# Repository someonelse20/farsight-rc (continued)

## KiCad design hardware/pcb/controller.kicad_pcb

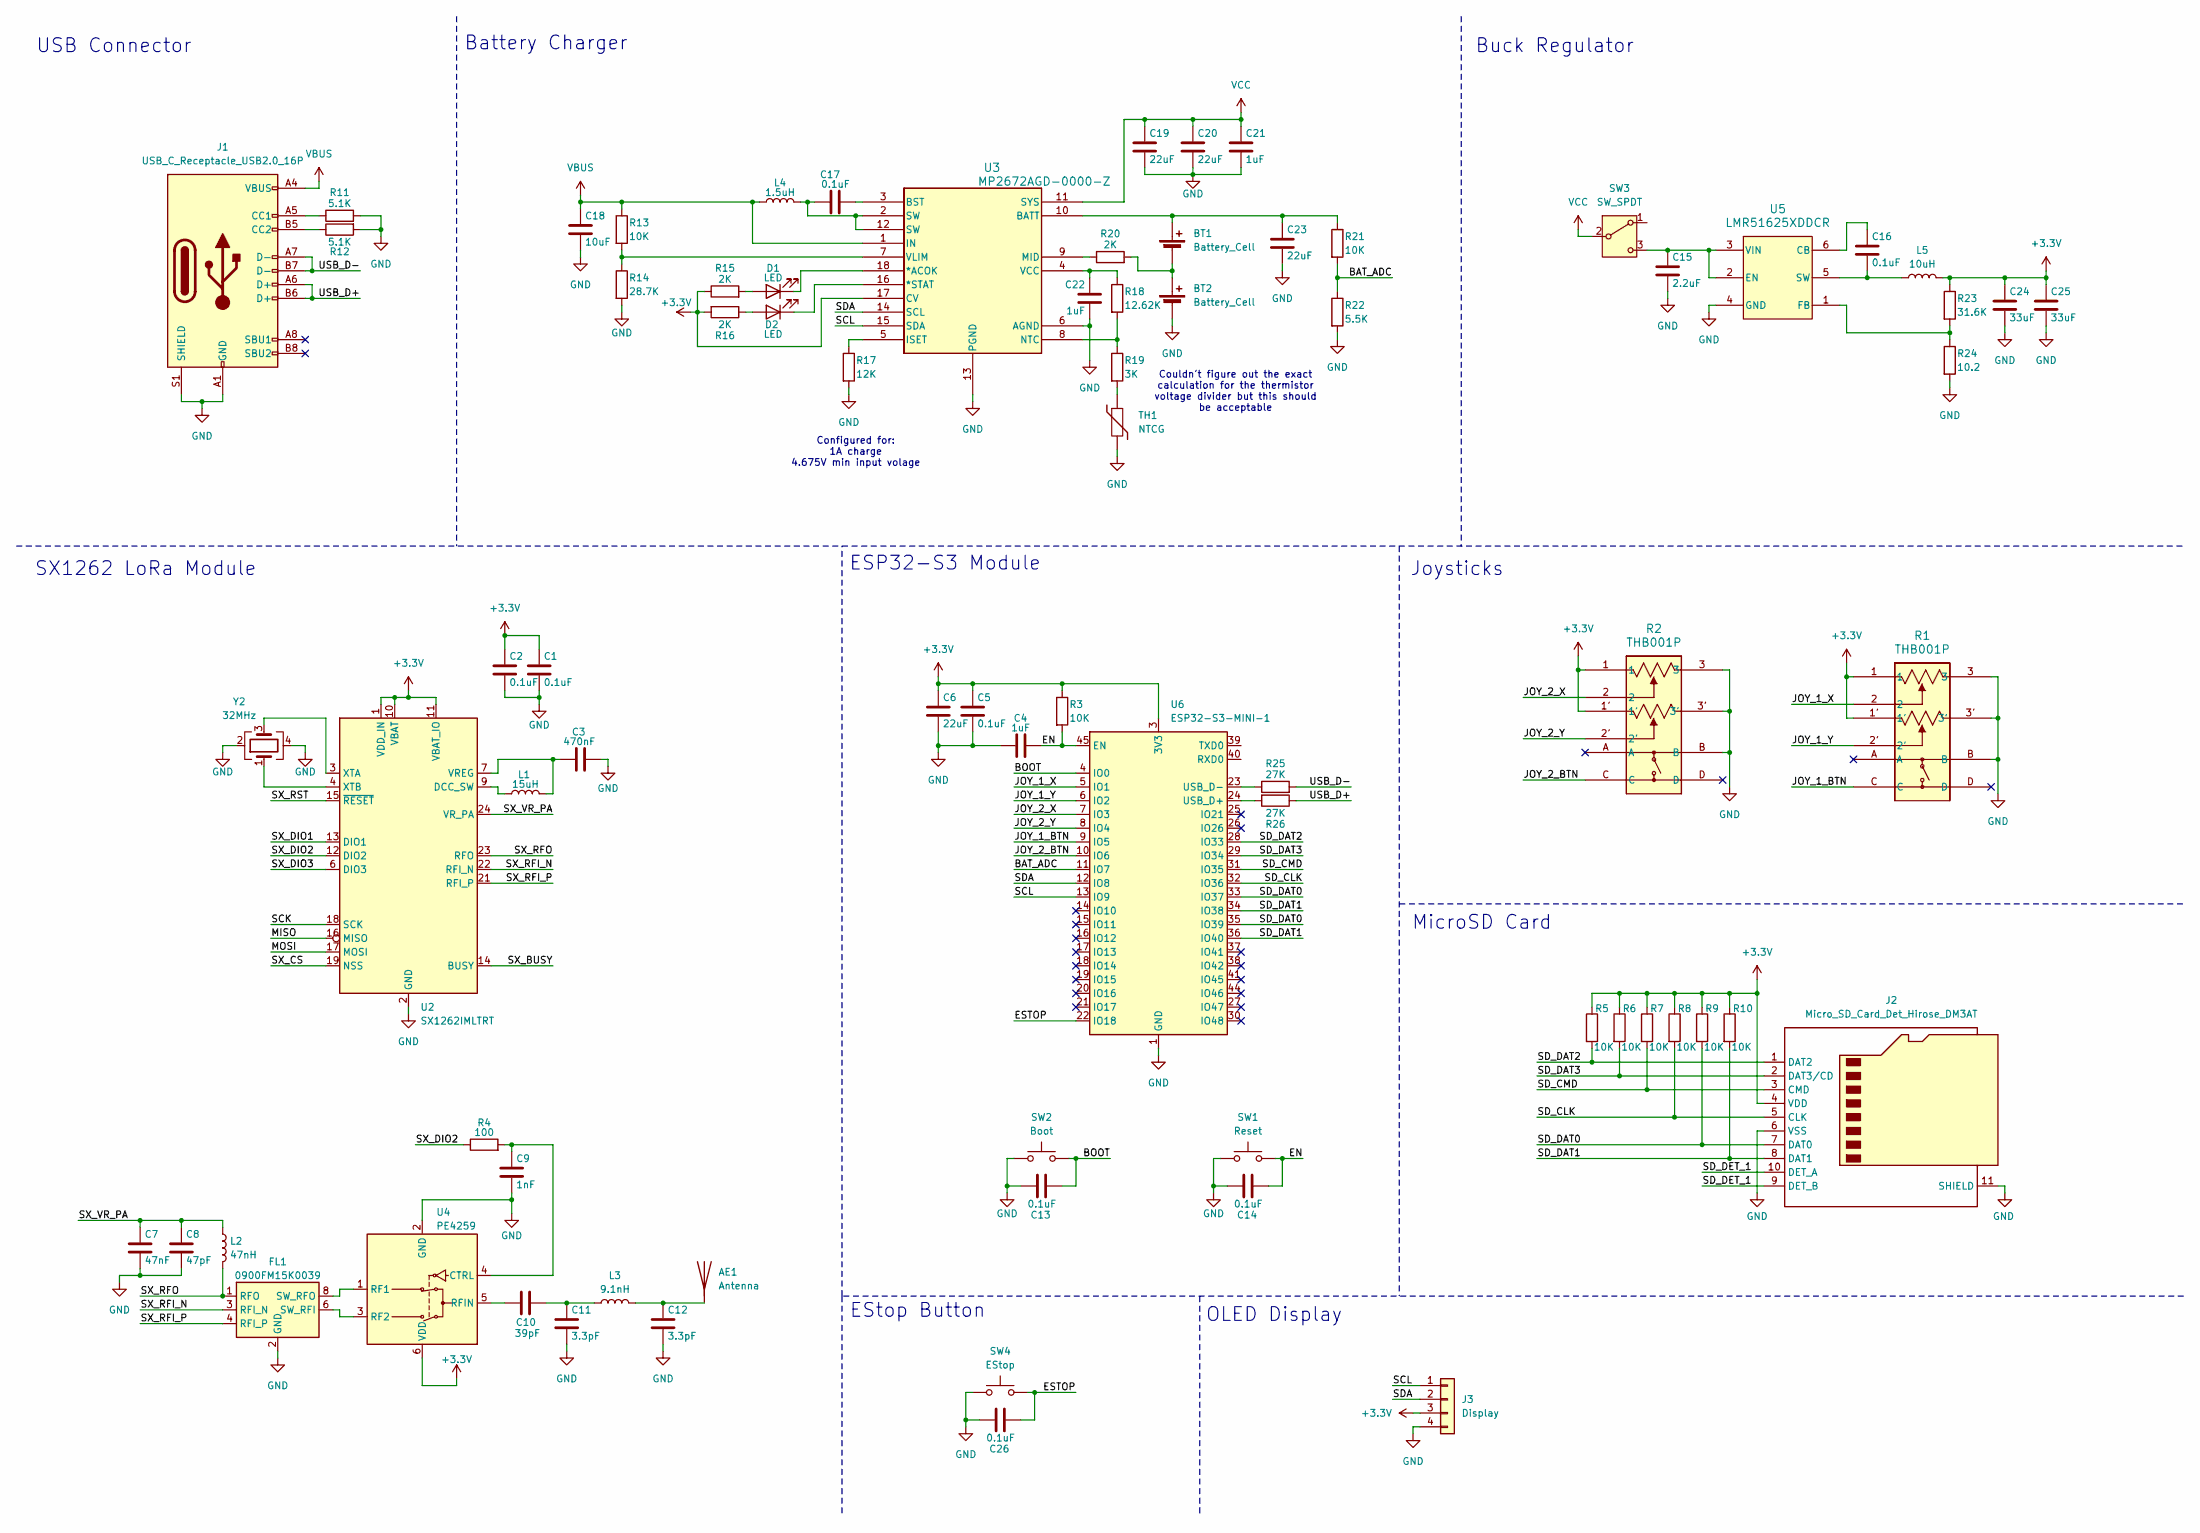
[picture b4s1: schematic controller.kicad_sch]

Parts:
AE1: Antenna; SMA_Amphenol_901-143_Horizontal
BT1, BT2: Battery_Cell; BatteryHolder_MPD_BH-18650-PC
C1, C2, C5, C13, C14, C16, C17, C26: 0.1uF; C_0402_1005Metric
C3: 470nF; C_0402_1005Metric
C4, C21, C22: 1uF; C_0402_1005Metric
C6, C19, C20: 22uF; C_0603_1608Metric
C7: 47nF; C_0402_1005Metric
C8: 47pF; C_0402_1005Metric
C9: 1nF; C_0402_1005Metric
C10: 39pF; C_0402_1005Metric
C11, C12: 3.3pF; C_0402_1005Metric
C15: 2.2uF; C_0402_1005Metric
C18: 10uF; C_0603_1608Metric
C23: 22uF; C_0805_2012Metric
C24, C25: 33uF; C_0603_1608Metric
D1, D2: LED; LED_D3.0mm
FL1: 0900FM15K0039; Balun_Johanson_0900FM15K0039
J1: USB_C_Receptacle_USB2.0_16P; USB_C_Receptacle_GCT_USB4105-xx-A_16P_TopMnt_Horizontal
J2: Micro_SD_Card_Det_Hirose_DM3AT; microSD_HC_Hirose_DM3AT-SF-PEJM5
J3: Display; JST_PH_S4B-PH-K_1x04_P2.00mm_Horizontal
L1: 15uH; L_0402_1005Metric
L2: 47nH; L_0402_1005Metric
L3: 9.1nH; L_0402_1005Metric
L4: 1.5uH; L_6.3x6.3_H3
L5: 10uH; L_APV_ANR4010
R1, R2: THB001P; THB001P_CNK
R3, R5, R6, R7, R8, R9, R10, R13, R21: 10K; R_0402_1005Metric
R4: 100; R_0402_1005Metric
R11, R12: 5.1K; R_0402_1005Metric
R14: 28.7K; R_0402_1005Metric
R15, R16, R20: 2K; R_0402_1005Metric
R17: 12K; R_0402_1005Metric
R18: 12.62K; R_0402_1005Metric
R19: 3K; R_0402_1005Metric
R22: 5.5K; R_0402_1005Metric
R23: 31.6K; R_0402_1005Metric
R24: 10.2; R_0402_1005Metric
R25, R26: 27K; R_0402_1005Metric
SW1: Reset; SW_Push_SPST_NO_Alps_SKRK
SW2: Boot; SW_Push_SPST_NO_Alps_SKRK
SW3: SW_SPDT; SW_Slide_SPDT_Straight_CK_OS102011MS2Q
SW4: EStop; SW_Push_SPST_NO_Alps_SKRK
TH1: NTCG; R_0402_1005Metric
U2: SX1262IMLTRT; QFN-24-1EP_4x4mm_P0.5mm_EP2.6x2.6mm
U3: MP2672AGD-0000-Z; QFN-18_MP2672A_MNP
U4: PE4259; SOT-363_SC-70-6
U5: LMR51625XDDCR; SOT-23-6
U6: ESP32-S3-MINI-1; ESP32-S2-MINI-1
Y2: 32MHz; Crystal_SMD_3225-4Pin_3.2x2.5mm

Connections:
+3.3V: C1.1, C2.1, C5.1, C6.1, C24.1, C25.1, J2.4 (VDD), J3.3, L5.2, R1.1, R1.1', R2.1, R2.1', R3.1, R5.1, R6.1, R7.1, R8.1, R9.1, R10.1, R15.1, R16.2, R23.1, U2.1 (VDD_IN), U2.10 (VBAT), U2.11 (VBAT_IO), U3.17 (CV), U4.6 (VDD), U6.3 (3V3)
/BAT_ADC: R21.2, R22.1, U6.11 (IO7)
/BOOT: C13.2, SW2.2, U6.4 (IO0)
/EN: C4.2, C14.2, R3.2, SW1.2, U6.45 (EN)
/ESTOP: C26.2, SW4.2, U6.22 (IO18)
/JOY_1_BTN: R1.C, U6.9 (IO5)
/JOY_1_X: R1.2, U6.5 (IO1)
/JOY_1_Y: R1.2', U6.6 (IO2)
/JOY_2_BTN: R2.C, U6.10 (IO6)
/JOY_2_X: R2.2, U6.7 (IO3)
/JOY_2_Y: R2.2', U6.8 (IO4)
/MISO: U2.16 (MISO)
/MOSI: U2.17 (MOSI)
/SCK: U2.18 (SCK)
/SCL: J3.1, U3.15 (SDA), U6.13 (IO9)
/SDA: J3.2, U3.14 (SCL), U6.12 (IO8)
/SD_CLK: J2.5 (CLK), R8.2, U6.32 (IO36)
/SD_CMD: J2.3 (CMD), R7.2, U6.31 (IO35)
/SD_DAT0: J2.7 (DAT0), R9.2, U6.33 (IO37), U6.35 (IO39)
/SD_DAT1: J2.8 (DAT1), R10.2, U6.34 (IO38), U6.36 (IO40)
/SD_DAT2: J2.1 (DAT2), R5.2, U6.28 (IO33)
/SD_DAT3: J2.2 (DAT3/CD), R6.2, U6.29 (IO34)
/SD_DET_1: J2.9 (DET_B), J2.10 (DET_A)
/SX_BUSY: U2.14 (BUSY)
/SX_CS: U2.19 (NSS)
/SX_DIO1: U2.13 (DIO1)
/SX_DIO2: R4.1, U2.12 (DIO2)
/SX_DIO3: U2.6 (DIO3)
/SX_RFI_N: FL1.3 (RFI_N), U2.22 (RFI_N)
/SX_RFI_P: FL1.4 (RFI_P), U2.21 (RFI_P)
/SX_RFO: FL1.1 (RFO), L2.2, U2.23 (RFO)
/SX_RST: U2.15 (~RESET)
/SX_VR_PA: C7.1, C8.1, L2.1, U2.24 (VR_PA)
/USB_D+: J1.A6 (D+), J1.B6 (D+), R26.1
/USB_D-: J1.A7 (D-), J1.B7 (D-), R25.2
GND: BT2.2 (-), C1.2, C2.2, C3.2, C4.1, C5.2, C6.2, C7.2, C8.2, C9.2, C11.2, C12.2, C13.1, C14.1, C15.2, C18.2, C19.2, C20.2, C21.2, C22.2, C23.2, C24.2, C25.2, C26.1, FL1.2 (GND), FL1.5 (GND), FL1.7 (GND), FL1.9 (GND), FL1.10 (GND), J1.A1 (GND), J1.A12 (GND), J1.B1 (GND), J1.B12 (GND), J1.S1 (SHIELD), J2.6 (VSS), J2.11 (SHIELD), J3.4, R1.3, R1.3', R1.B, R2.3, R2.3', R2.B, R11.2, R12.2, R14.2, R17.2, R22.2, R24.2, SW1.1, SW2.1, SW4.1, TH1.2, U2.2 (GND), U2.5 (GND), U2.8 (GND), U2.20 (GND), U2.25 (GND), U3.6 (AGND), U3.13 (PGND), U4.2 (GND), U5.4 (GND), U6.1 (GND), U6.2 (GND), U6.42 (GND), U6.43 (GND), U6.46 (GND), U6.47 (GND), U6.48 (GND), U6.49 (GND), U6.50 (GND), U6.51 (GND), U6.52 (GND), U6.53 (GND), U6.54 (GND), U6.55 (GND), U6.56 (GND), U6.57 (GND), U6.58 (GND), U6.59 (GND), U6.60 (GND), U6.61 (GND), U6.62 (GND), U6.63 (GND), U6.64 (GND), U6.65 (GND), Y2.2, Y2.4
unnamed: AE1.1 (A), C12.1, L3.2
unnamed: BT1.1 (+), C23.1, R21.1, U3.10 (BATT)
unnamed: BT1.2 (-), BT2.1 (+), R20.2
unnamed: C10.2, C11.1, L3.1
unnamed: C17.1, L4.2, U3.2 (SW), U3.12 (SW)
unnamed: D1.2 (A), R15.2
unnamed: D1.1 (K), U3.18 (*ACOK)
unnamed: D2.2 (A), R16.1
unnamed: D2.1 (K), U3.16 (*STAT)
unnamed: FL1.6 (SW_RFI), U4.3 (RF2)
unnamed: FL1.8 (SW_RFO), U4.1 (RF1)
unnamed: J1.A5 (CC1), R11.1
unnamed: J1.B5 (CC2), R12.1
unnamed: R19.2, TH1.1
unnamed: C15.1, SW3.3 (C), U5.2 (EN), U5.3 (VIN)
unnamed: L1.1, U2.9 (DCC_SW)
unnamed: C3.1, L1.2, U2.7 (VREG)
unnamed: U2.3 (XTA), Y2.3
unnamed: U2.4 (XTB), Y2.1
unnamed: C17.2, U3.3 (BST)
unnamed: R17.1, U3.5 (ISET)
unnamed: R20.1, U3.9 (MID)
unnamed: R18.2, R19.1, U3.8 (NTC)
unnamed: C22.1, R18.1, U3.4 (VCC)
unnamed: R13.2, R14.1, U3.7 (VLIM)
unnamed: C9.1, R4.2, U4.4 (CTRL)
unnamed: C10.1, U4.5 (RFIN)
unnamed: C16.1, U5.6 (CB)
unnamed: R23.2, R24.1, U5.1 (FB)
unnamed: C16.2, L5.1, U5.5 (SW)
unnamed: R26.2, U6.24 (USB_D+)
unnamed: R25.1, U6.23 (USB_D-)
VBUS: C18.1, J1.A4 (VBUS), J1.A9 (VBUS), J1.B4 (VBUS), J1.B9 (VBUS), L4.1, R13.1, U3.1 (IN)
VCC: C19.1, C20.1, C21.1, SW3.2 (B), U3.11 (SYS)

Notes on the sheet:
Buck Regulator
ESP32-S3 Module
Joysticks
EStop Button
Couldn't figure out the exact calculation for the thermistor voltage divider but this should be acceptable
USB Connector
Battery Charger
SX1262 LoRa Module
OLED Display
Configured for: 1A charge 4.675V min input volage
MicroSD Card

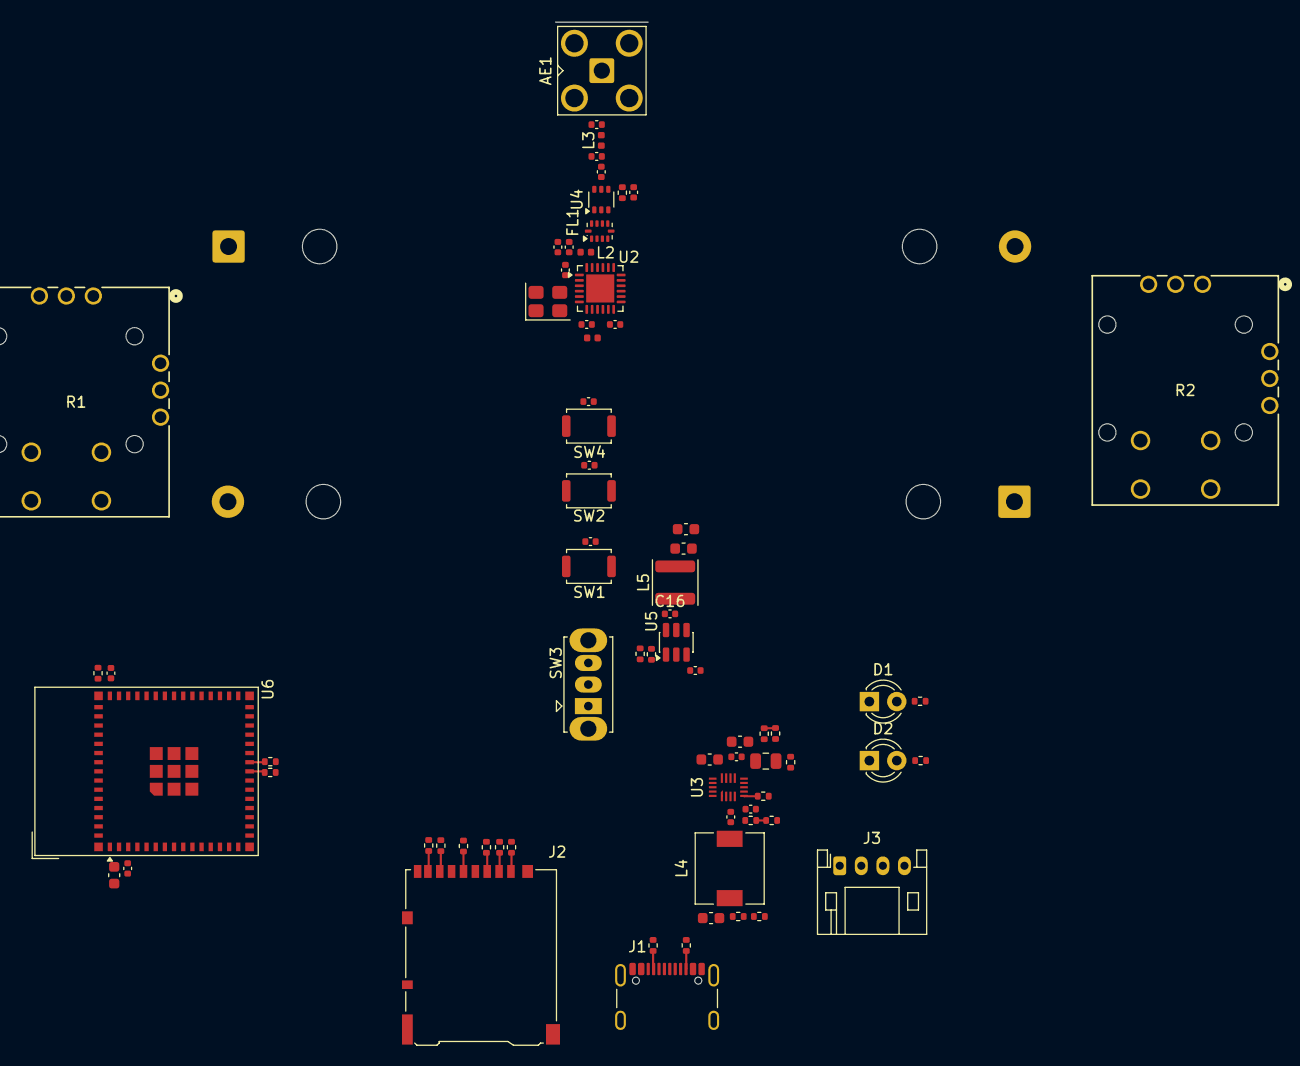
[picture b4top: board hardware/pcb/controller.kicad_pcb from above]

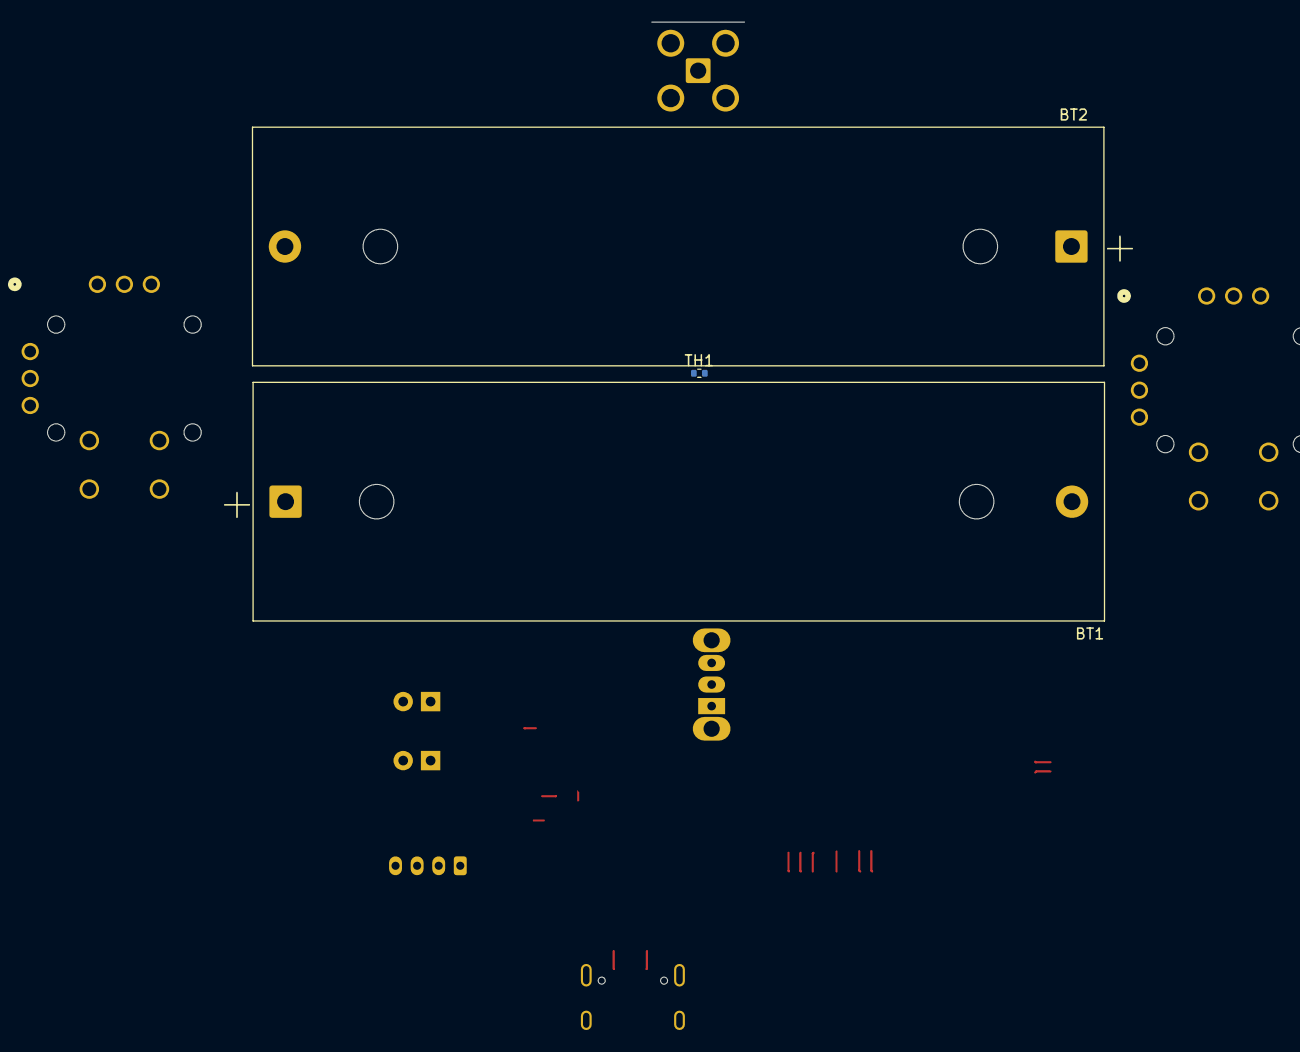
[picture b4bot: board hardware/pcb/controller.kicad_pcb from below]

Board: 4 copper layers, 77 parts (3 on the bottom side), 62 nets.

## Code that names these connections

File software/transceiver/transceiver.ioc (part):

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Mcu.Name=STM32U535CCUx
Mcu.Package=UFQFPN48
Mcu.UserName=STM32U535CCUx
PA1.Mode=Full_Duplex_Master
PA1.Signal=SPI1_SCK
PA10.Mode=Asynchronous
PA10.Signal=USART1_RX
PA13\ (JTMS/SWDIO).Mode=Serial_Wire
PA13\ (JTMS/SWDIO).Signal=DEBUG_JTMS-SWDIO
PA14\ (JTCK/SWCLK).Mode=Serial_Wire
PA14\ (JTCK/SWCLK).Signal=DEBUG_JTCK-SWCLK
PA4.Mode=NSS_Signal_Hard_Output
PA4.Signal=SPI1_NSS
PA6.Mode=Full_Duplex_Master
PA6.Signal=SPI1_MISO
PA7.Mode=Full_Duplex_Master
PA7.Signal=SPI1_MOSI
PA9.Mode=Asynchronous
PA9.Signal=USART1_TX
PB0.Signal=GPIO_Output
PB1.Signal=GPIO_Input
PB2.Signal=GPXTI2
PB9.Signal=GPIO_Output
PC14-OSC32_IN\ (PC14).Mode=LSE-External-Oscillator-for-RTC
PC14-OSC32_IN\ (PC14).Signal=RCC_OSC32_IN
PC15-OSC32_OUT\ (PC15).Mode=LSE-External-Oscillator-for-RTC
PC15-OSC32_OUT\ (PC15).Signal=RCC_OSC32_OUT
PH0-OSC_IN\ (PH0).Mode=HSE-External-Oscillator
PH0-OSC_IN\ (PH0).Signal=RCC_OSC_IN
PH1-OSC_OUT\ (PH1).Mode=HSE-External-Oscillator
PH1-OSC_OUT\ (PH1).Signal=RCC_OSC_OUT
RCC.HSE_VALUE=16000000
board=custom

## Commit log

2026-02-08 started wiring schematic
2026-02-09 finished schematic
2026-02-09 added footprints
2026-02-09 added footprints and started layout
2026-02-09 routing board
2026-02-14 finished first version
2026-02-14 finished board
2026-02-16 started cad
2026-02-18 added tranceiver and joystick
2026-02-19 added ap and http server
2026-02-19 added gitignore
2026-02-19 cleaning up code
2026-02-20 added oled driver
2026-02-21 redesigned tranceiver
2026-02-22 updated controller pcb
2026-02-22 cleaning up transceiver
2026-02-22 adding software for transceiver
2026-02-22 cleaning up controller pcb
2026-02-23 fixed tansceiver cmake
2026-02-23 added basic lora functionality
2026-02-24 added print
2026-02-24 updated cad
2026-02-24 touching up hardware
2026-02-26 working on transceiver firmware
2026-02-26 updated joystick
2026-02-26 added settings
2026-02-26 fixed wakeup function
2026-02-26 added logging
2026-02-26 added lines to schematic
2026-02-28 changing uart communication
2026-02-28 changed switch circuit
2026-03-02 fixing switch
2026-03-02 added uart protocol
2026-03-02 fixed switch and joysticks
2026-03-02 fixed switch and joystick
2026-03-03 moved reg.c/h to uart_reg.c/h
2026-03-03 fixed sx126x hal read
2026-03-03 added SWD to transceiver
2026-03-05 fixed usb
2026-03-05 added assets
2026-03-05 changed boot1 and reset1 to boot and reset
2026-03-07 Update BOM
2026-03-07 Updated BOM
2026-03-07 added production files
2026-03-07 added bom.csv
2026-03-08 added version to silkscreen
2026-03-08 Added display to BOM
2026-03-08 added oled to bom
2026-03-16 added who am i register
2026-03-16 fixed readme
2026-03-16 added variable sized packets
2026-03-16 added continuous rx
2026-03-29 rewriting controller firmware
2026-03-30 rewrote firmware
2026-03-30 writing adc
2026-03-30 added adc polling
2026-04-02 updated to kicad 10
2026-04-02 changed to stm32u535cc
